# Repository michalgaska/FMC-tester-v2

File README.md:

# FMC-tester-v2

FMC tester v2 based on the original design done by Tomasz Wlostowski at CERN. The project was transferred to Kicad for Berkeley Lab.  
The following changes have been made:
- IO expanders were changed to MAX7312
- added resistors connecting _N and _P lines for each differential pair in the HPC signal group

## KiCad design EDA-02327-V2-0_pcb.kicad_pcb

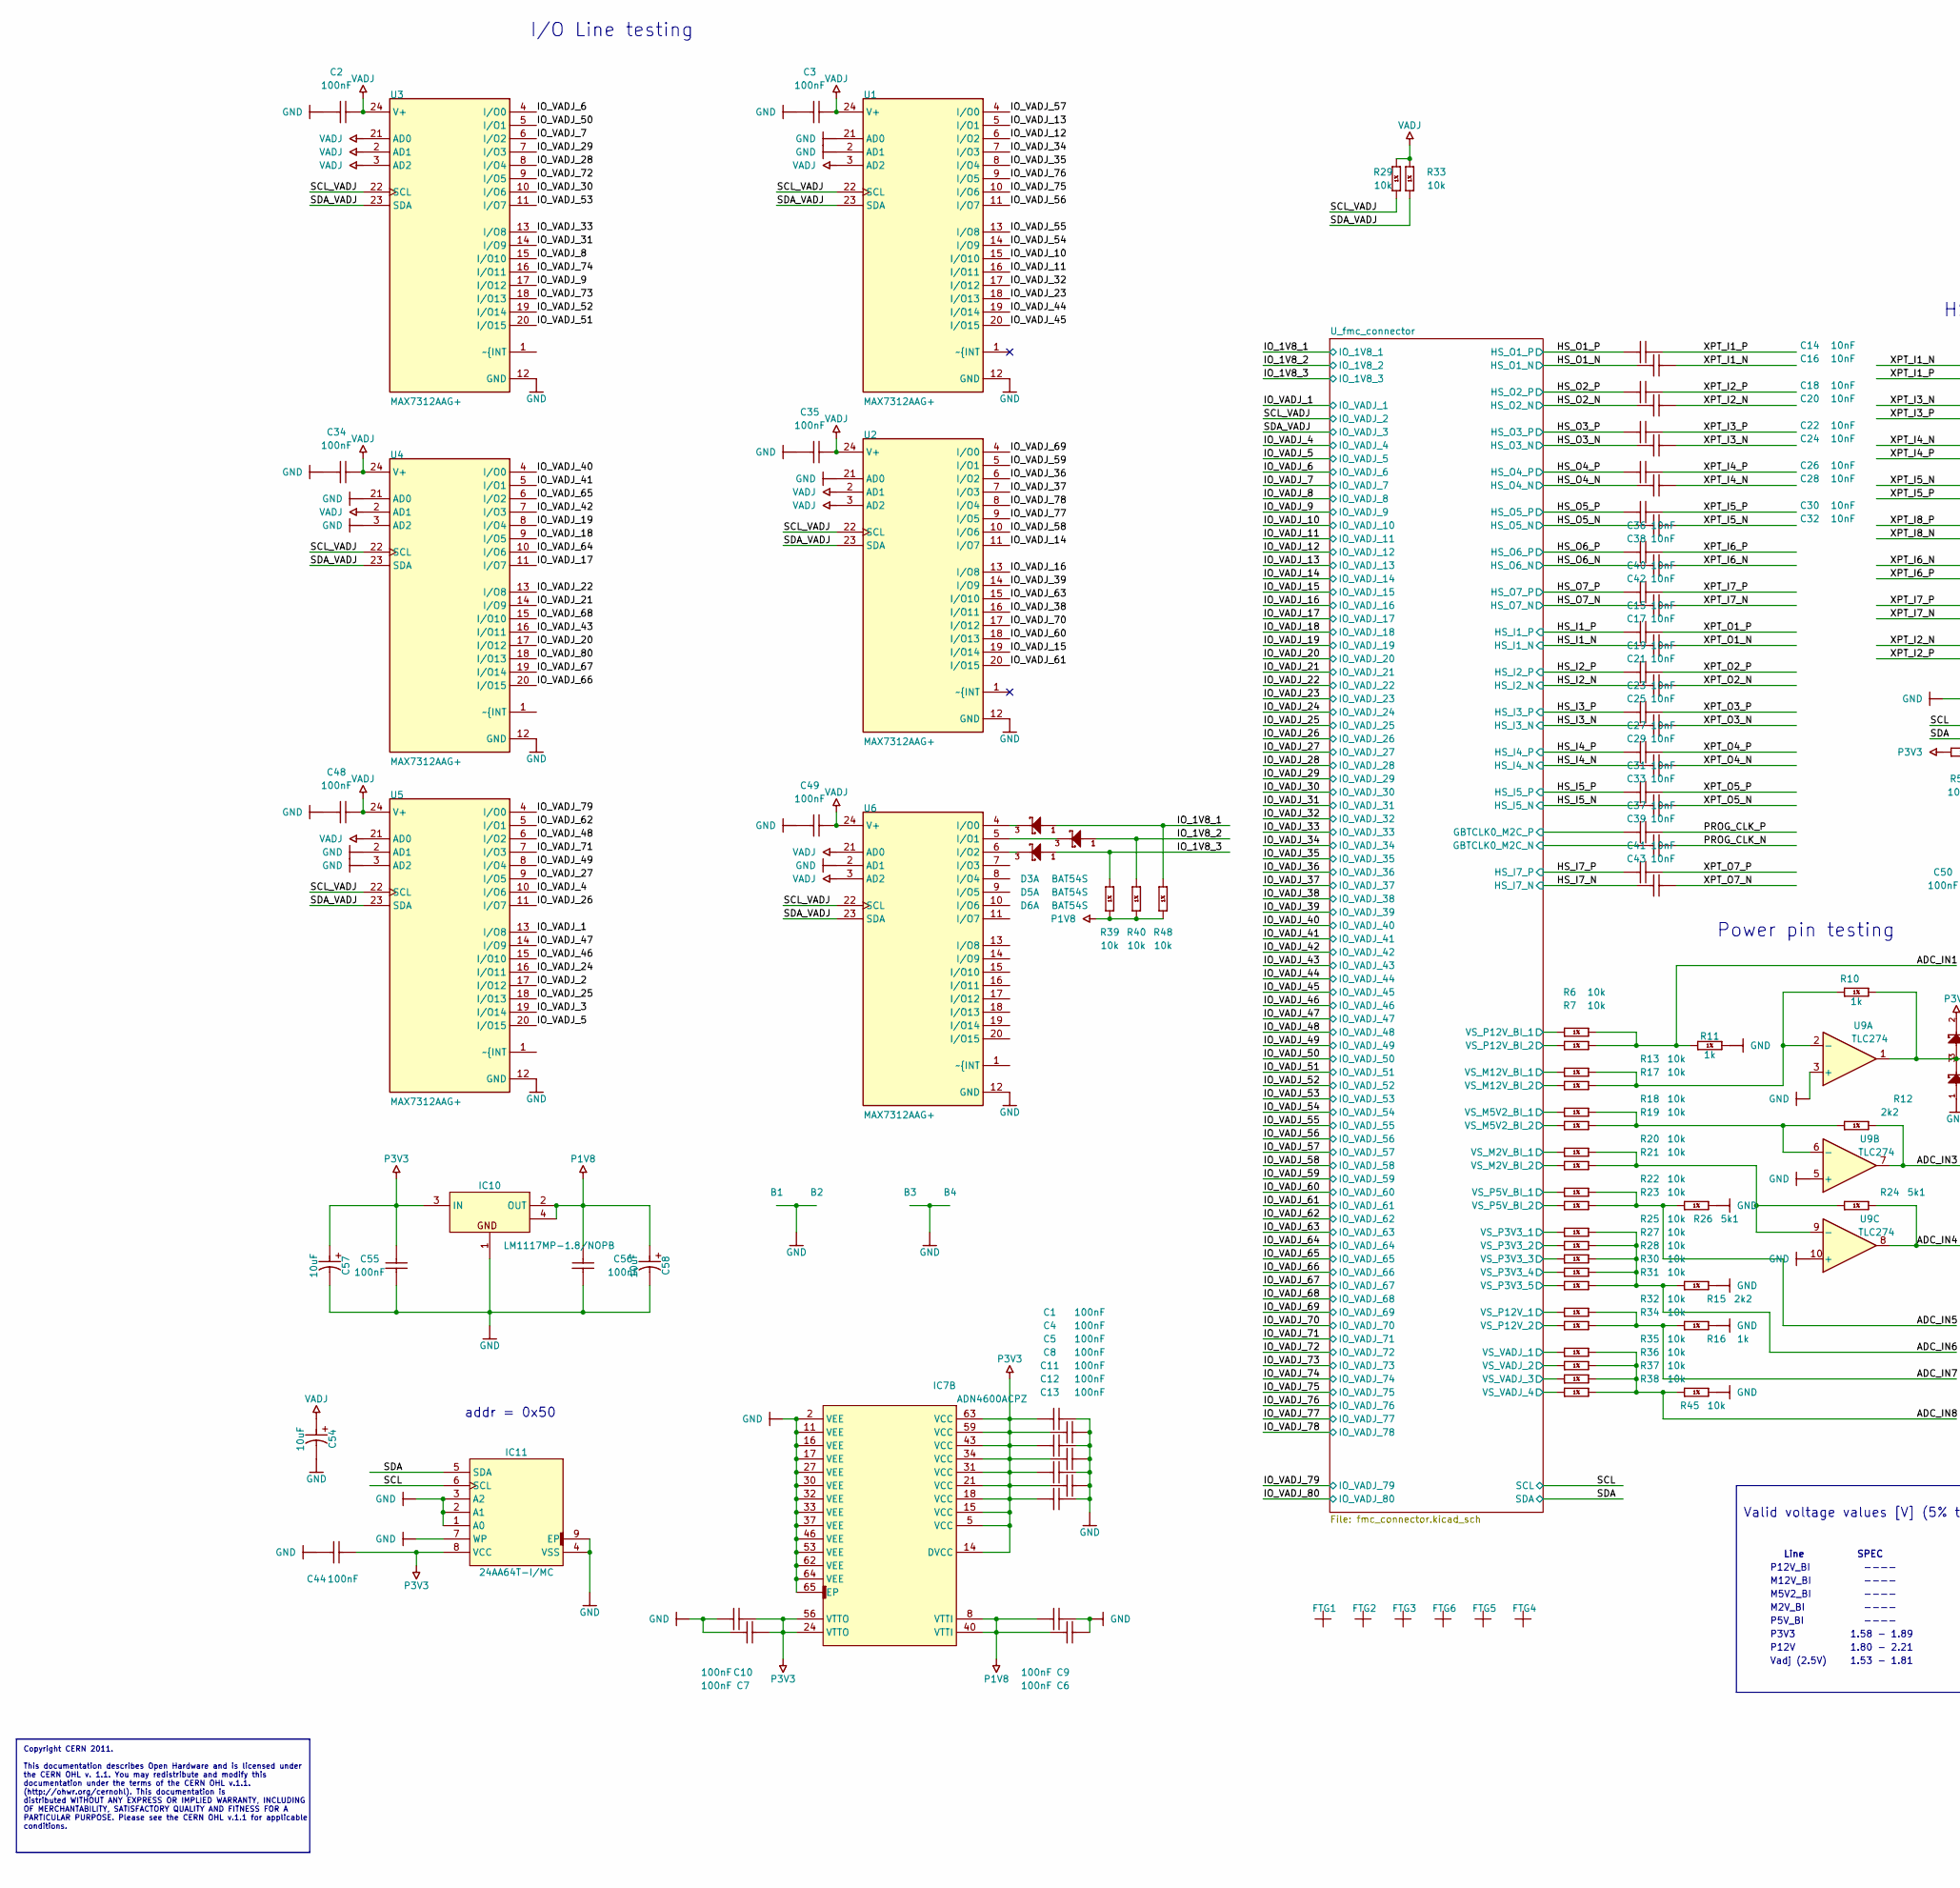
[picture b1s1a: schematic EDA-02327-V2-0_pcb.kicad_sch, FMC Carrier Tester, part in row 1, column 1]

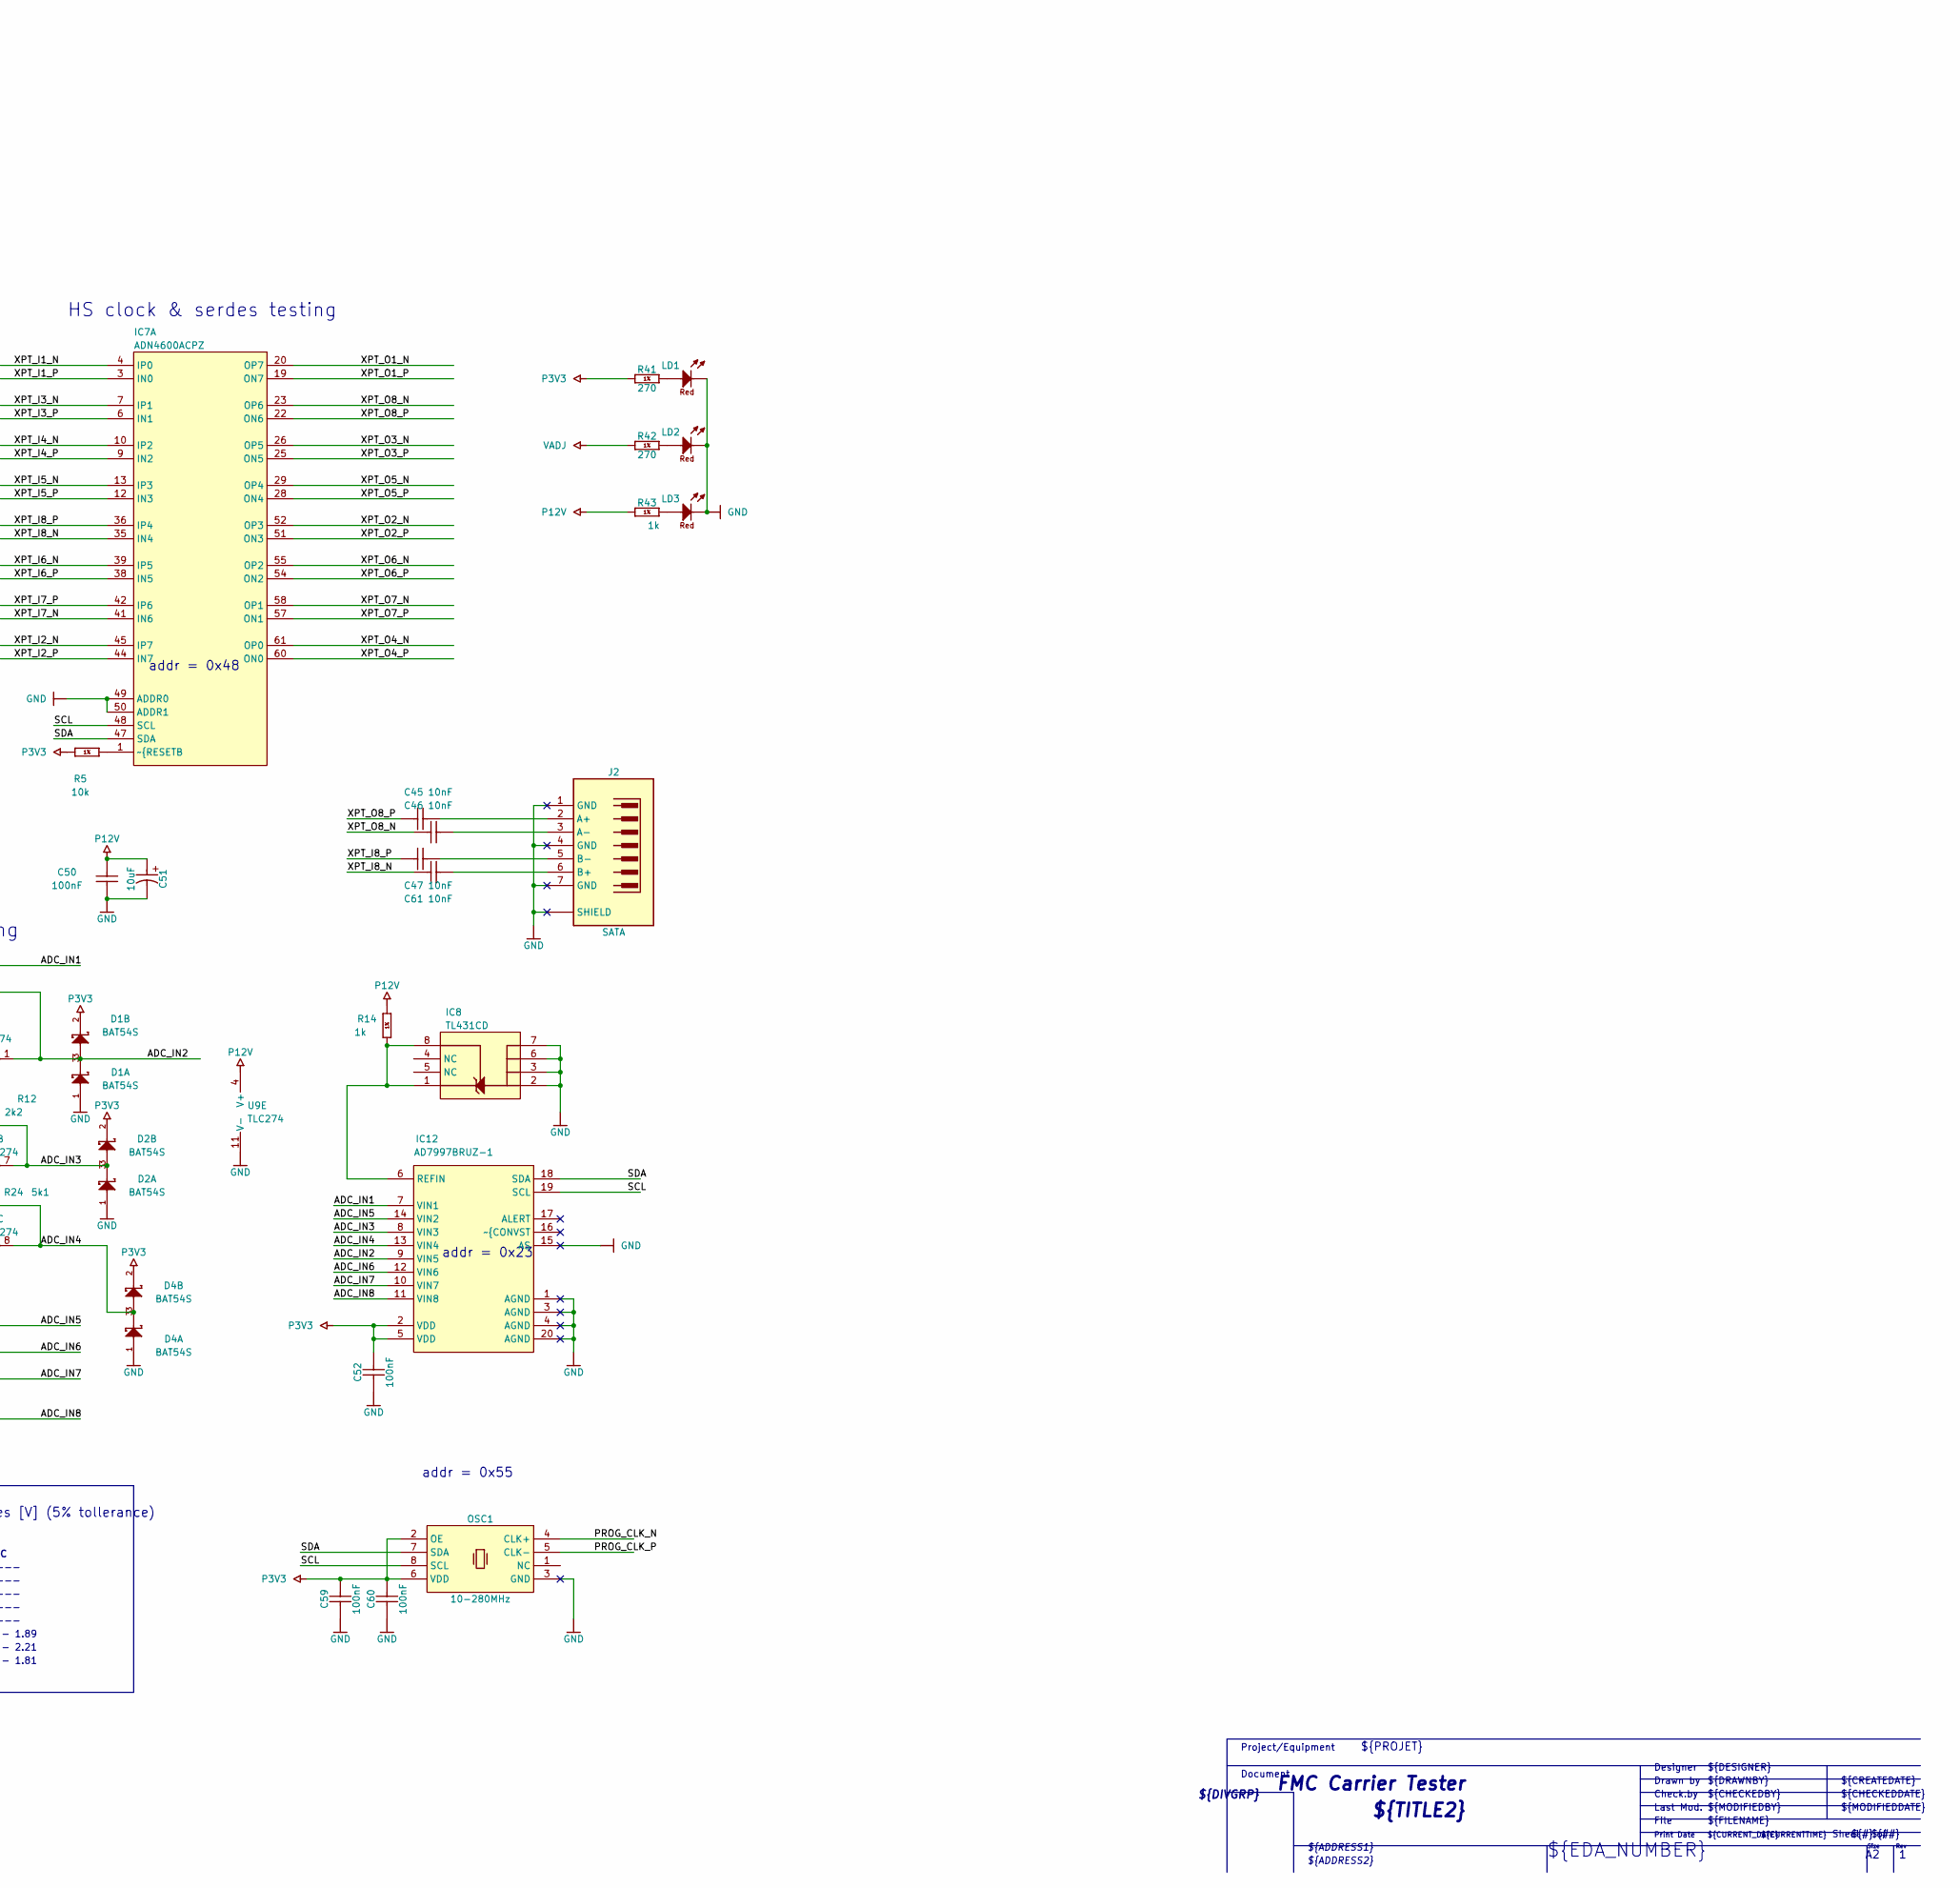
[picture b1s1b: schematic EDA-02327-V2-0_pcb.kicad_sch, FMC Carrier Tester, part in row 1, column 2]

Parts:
B1, B2, B3, B4: Plated Hole; MTG300_600; PART NUMBER PLATED_HOLE3.0_PAD6.0
C1, C2, C3, C4, C5, C6, C7, C8, C9, C10, C11, C12, C13, C34, C35, C44, C48, C49, C50, C52, C55, C56, C59, C60: 100nF; CAPC1608X87N; VOLTAGE 50V; TOLERANCE ±10%; PART NUMBER CC0603_100NF_50V_10%_X7R
C14, C15, C16, C17, C18, C19, C20, C21, C22, C23, C24, C25, C26, C27, C28, C29, C30, C31, C32, C33, C36, C37, C38, C39, C40, C41, C42, C43, C45, C46, C47, C61: 10nF; CAPC1005X55N; VOLTAGE 16V; TOLERANCE ±10%; PART NUMBER CC0402_10NF_16V_10%_X7R
C51, C54, C57, C58: 10uF; CAPMP3528X210N; VOLTAGE 16V; TOLERANCE ±10%; PART NUMBER CTE3528-21_10UF_16V_10%_LESR0800
D1, D2, D3, D4, D5, D6: BAT54S; SOT95P240X130-3N; VOLTAGE 30V; PART NUMBER BAT54S
FTG1, FTG2, FTG3, FTG4, FTG5, FTG6: Use only in PCB; FIDUCIAL_TOP_S100-200; PART NUMBER FIDUCIAL_TARGET_S100-200
IC7: ADN4600ACPZ; QFN50P900X900X100-65N-S615; PART NUMBER ADN4600ACPZ
IC8: TL431CD; SOIC127P600X175-8N; PART NUMBER TL431CD
IC10: LM1117MP-1.8/NOPB; SOT230P700X180-4N; PART NUMBER LM1117MP-1.8/NOPB
IC11: 24AA64T-I/MC; SON50P300X200X100-9N-S175X155; PART NUMBER 24AA64T-I/MC
IC12: AD7997BRUZ-1; SOP65P640X120-20N; PART NUMBER AD7997BRUZ-1
J2: SATA; 3M_5607-4200-SH; PART NUMBER 3M_5607-4200-SH
LD1, LD2, LD3: Red; LEDC1608X80N_RED; PART NUMBER LED_ROHM_SML-311UTT86K
OSC1: 10-280MHz; OSC_SILICON-LAB_SI570; PART NUMBER OSC_10-280MHZ_SILICON-LAB_Si570BBC00012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
R5, R6, R7, R13, R17, R18, R19, R20, R21, R22, R23, R25, R27, R28, R29, R30, R31, R32, R33, R34, R35, R36, R37, R38, R39, R40, R45, R48: 10k; RESC1608X55N; TOLERANCE ±1%; PART NUMBER R0603_10K_1%_0.1W_100PPM
R10, R11, R14, R16, R43: 1k; RESC1608X55N; TOLERANCE ±1%; PART NUMBER R0603_1K_1%_0.1W_100PPM
R12, R15: 2k2; RESC1608X55N; TOLERANCE ±1%; PART NUMBER R0603_2K2_1%_0.1W_100PPM
R24, R26: 5k1; RESC1608X55N; TOLERANCE ±1%; PART NUMBER R0603_5K1_1%_0.1W_100PPM
R41, R42: 270; RESC1608X55N; TOLERANCE ±1%; PART NUMBER R0603_270R_1%_0.1W_100PPM
U1, U2, U3, U4, U5, U6: MAX7312AAG+; FP-A24-2-MFG
U9: TLC274; SOIC-14_3.9x8.7mm_P1.27mm

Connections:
/ADC_IN1: IC12.7 (VIN1), R6.2, R7.2, R11.1
/ADC_IN2: D1.3 (COMAC), IC12.9 (VIN5), R10.2, U9.1
/ADC_IN3: D2.3 (COMAC), IC12.8 (VIN3), R12.2, U9.7
/ADC_IN4: D4.3 (COMAC), IC12.13 (VIN4), R24.2, U9.8
/ADC_IN5: IC12.14 (VIN2), R22.2, R23.2, R26.1
/ADC_IN6: IC12.12 (VIN6), R15.1, R25.2, R27.2, R28.2, R30.2, R31.2
/ADC_IN7: IC12.10 (VIN7), R16.1, R32.2, R34.2
/ADC_IN8: IC12.11 (VIN8), R35.2, R36.2, R37.2, R38.2, R45.1
/HS_I1_N: C17.1; also elsewhere on the board
/HS_I1_P: C15.1; also elsewhere on the board
/HS_I2_N: C21.1; also elsewhere on the board
/HS_I2_P: C19.1; also elsewhere on the board
/HS_I3_N: C25.1; also elsewhere on the board
/HS_I3_P: C23.1; also elsewhere on the board
/HS_I4_N: C29.1; also elsewhere on the board
/HS_I4_P: C27.1; also elsewhere on the board
/HS_I5_N: C33.1; also elsewhere on the board
/HS_I5_P: C31.1; also elsewhere on the board
/HS_I7_N: C43.1; also elsewhere on the board
/HS_I7_P: C41.1; also elsewhere on the board
/HS_O1_N: C16.1; also elsewhere on the board
/HS_O1_P: C14.1; also elsewhere on the board
/HS_O2_N: C20.1; also elsewhere on the board
/HS_O2_P: C18.1; also elsewhere on the board
/HS_O3_N: C24.1; also elsewhere on the board
/HS_O3_P: C22.1; also elsewhere on the board
/HS_O4_N: C28.1; also elsewhere on the board
/HS_O4_P: C26.1; also elsewhere on the board
/HS_O5_N: C32.1; also elsewhere on the board
/HS_O5_P: C30.1; also elsewhere on the board
/HS_O6_N: C38.1; also elsewhere on the board
/HS_O6_P: C36.1; also elsewhere on the board
/HS_O7_N: C42.1; also elsewhere on the board
/HS_O7_P: C40.1; also elsewhere on the board
/IO_1V8_1: D5.1 (A), R48.2; also elsewhere on the board
/IO_1V8_2: D6.1 (A), R40.2; also elsewhere on the board
/IO_1V8_3: D3.1 (A), R39.2; also elsewhere on the board
/IO_VADJ_1: U5.13 (I/O8); also elsewhere on the board
/IO_VADJ_2: U5.17 (I/O12)
/IO_VADJ_3: U5.19 (I/O14)
/IO_VADJ_4: U5.10 (I/O6); also elsewhere on the board
/IO_VADJ_5: U5.20 (I/O15); also elsewhere on the board
/IO_VADJ_6: U3.4 (I/O0); also elsewhere on the board
/IO_VADJ_7: U3.6 (I/O2); also elsewhere on the board
/IO_VADJ_8: U3.15 (I/O10); also elsewhere on the board
/IO_VADJ_9: U3.17 (I/O12); also elsewhere on the board
/IO_VADJ_10: U1.15 (I/O10); also elsewhere on the board
/IO_VADJ_11: U1.16 (I/O11); also elsewhere on the board
/IO_VADJ_12: U1.6 (I/O2); also elsewhere on the board
/IO_VADJ_13: U1.5 (I/O1); also elsewhere on the board
/IO_VADJ_14: U2.11 (I/O7); also elsewhere on the board
/IO_VADJ_15: U2.19 (I/O14); also elsewhere on the board
/IO_VADJ_16: U2.13 (I/O8); also elsewhere on the board
/IO_VADJ_17: U4.11 (I/O7); also elsewhere on the board
/IO_VADJ_18: U4.9 (I/O5); also elsewhere on the board
/IO_VADJ_19: U4.8 (I/O4); also elsewhere on the board
/IO_VADJ_20: U4.17 (I/O12); also elsewhere on the board
/IO_VADJ_21: U4.14 (I/O9); also elsewhere on the board
/IO_VADJ_22: U4.13 (I/O8); also elsewhere on the board
/IO_VADJ_23: U1.18 (I/O13); also elsewhere on the board
/IO_VADJ_24: U5.16 (I/O11); also elsewhere on the board
/IO_VADJ_25: U5.18 (I/O13); also elsewhere on the board
/IO_VADJ_26: U5.11 (I/O7); also elsewhere on the board
/IO_VADJ_27: U5.9 (I/O5); also elsewhere on the board
/IO_VADJ_28: U3.8 (I/O4); also elsewhere on the board
/IO_VADJ_29: U3.7 (I/O3); also elsewhere on the board
/IO_VADJ_30: U3.10 (I/O6); also elsewhere on the board
/IO_VADJ_31: U3.14 (I/O9); also elsewhere on the board
/IO_VADJ_32: U1.17 (I/O12); also elsewhere on the board
/IO_VADJ_33: U3.13 (I/O8); also elsewhere on the board
/IO_VADJ_34: U1.7 (I/O3); also elsewhere on the board
/IO_VADJ_35: U1.8 (I/O4); also elsewhere on the board
/IO_VADJ_36: U2.6 (I/O2); also elsewhere on the board
/IO_VADJ_37: U2.7 (I/O3); also elsewhere on the board
/IO_VADJ_38: U2.16 (I/O11); also elsewhere on the board
/IO_VADJ_39: U2.14 (I/O9); also elsewhere on the board
/IO_VADJ_40: U4.4 (I/O0); also elsewhere on the board
/IO_VADJ_41: U4.5 (I/O1); also elsewhere on the board
/IO_VADJ_42: U4.7 (I/O3); also elsewhere on the board
/IO_VADJ_43: U4.16 (I/O11); also elsewhere on the board
/IO_VADJ_44: U1.19 (I/O14); also elsewhere on the board
/IO_VADJ_45: U1.20 (I/O15); also elsewhere on the board
/IO_VADJ_46: U5.15 (I/O10); also elsewhere on the board
/IO_VADJ_47: U5.14 (I/O9); also elsewhere on the board
/IO_VADJ_48: U5.6 (I/O2); also elsewhere on the board
/IO_VADJ_49: U5.8 (I/O4); also elsewhere on the board
/IO_VADJ_50: U3.5 (I/O1); also elsewhere on the board
/IO_VADJ_51: U3.20 (I/O15); also elsewhere on the board
/IO_VADJ_52: U3.19 (I/O14); also elsewhere on the board
/IO_VADJ_53: U3.11 (I/O7); also elsewhere on the board
/IO_VADJ_54: U1.14 (I/O9); also elsewhere on the board
/IO_VADJ_55: U1.13 (I/O8); also elsewhere on the board
/IO_VADJ_56: U1.11 (I/O7); also elsewhere on the board
/IO_VADJ_57: U1.4 (I/O0); also elsewhere on the board
/IO_VADJ_58: U2.10 (I/O6); also elsewhere on the board
/IO_VADJ_59: U2.5 (I/O1); also elsewhere on the board
/IO_VADJ_60: U2.18 (I/O13); also elsewhere on the board
/IO_VADJ_61: U2.20 (I/O15); also elsewhere on the board
/IO_VADJ_62: U5.5 (I/O1); also elsewhere on the board
/IO_VADJ_63: U2.15 (I/O10); also elsewhere on the board
/IO_VADJ_64: U4.10 (I/O6); also elsewhere on the board
/IO_VADJ_65: U4.6 (I/O2); also elsewhere on the board
/IO_VADJ_66: U4.20 (I/O15); also elsewhere on the board
/IO_VADJ_67: U4.19 (I/O14); also elsewhere on the board
/IO_VADJ_68: U4.15 (I/O10); also elsewhere on the board
/IO_VADJ_69: U2.4 (I/O0); also elsewhere on the board
/IO_VADJ_70: U2.17 (I/O12); also elsewhere on the board
/IO_VADJ_71: U5.7 (I/O3); also elsewhere on the board
/IO_VADJ_72: U3.9 (I/O5); also elsewhere on the board
/IO_VADJ_73: U3.18 (I/O13); also elsewhere on the board
/IO_VADJ_74: U3.16 (I/O11); also elsewhere on the board
/IO_VADJ_75: U1.10 (I/O6); also elsewhere on the board
/IO_VADJ_76: U1.9 (I/O5); also elsewhere on the board
/IO_VADJ_77: U2.9 (I/O5); also elsewhere on the board
/IO_VADJ_78: U2.8 (I/O4); also elsewhere on the board
/IO_VADJ_79: U5.4 (I/O0); also elsewhere on the board
/IO_VADJ_80: U4.18 (I/O13); also elsewhere on the board
/PROG_CLK_N: C39.2, OSC1.4 (CLK+)
/PROG_CLK_P: C37.2, OSC1.5 (CLK-)
/SCL: IC7.48 (SCL), IC11.6 (SCL), IC12.19 (SCL), OSC1.8 (SCL); also elsewhere on the board
/SCL_VADJ: R29.1, U1.22 (SCL), U2.22 (SCL), U3.22 (SCL), U4.22 (SCL), U5.22 (SCL), U6.22 (SCL); also elsewhere on the board
/SDA: IC7.47 (SDA), IC11.5 (SDA), IC12.18 (SDA), OSC1.7 (SDA); also elsewhere on the board
/SDA_VADJ: R33.1, U1.23 (SDA), U2.23 (SDA), U3.23 (SDA), U4.23 (SDA), U5.23 (SDA), U6.23 (SDA); also elsewhere on the board
/U_fmc_connector/GBTCLK0_M2C_N: C39.1; also elsewhere on the board
/U_fmc_connector/GBTCLK0_M2C_P: C37.1; also elsewhere on the board
/U_fmc_connector/VS_M2V_BI_1: R20.1; also elsewhere on the board
/U_fmc_connector/VS_M2V_BI_2: R21.1; also elsewhere on the board
/U_fmc_connector/VS_M5V2_BI_1: R18.1; also elsewhere on the board
/U_fmc_connector/VS_M5V2_BI_2: R19.1; also elsewhere on the board
/U_fmc_connector/VS_M12V_BI_1: R13.1; also elsewhere on the board
/U_fmc_connector/VS_M12V_BI_2: R17.1; also elsewhere on the board
/U_fmc_connector/VS_P3V3_1: R25.1; also elsewhere on the board
/U_fmc_connector/VS_P3V3_2: R27.1; also elsewhere on the board
/U_fmc_connector/VS_P3V3_3: R28.1; also elsewhere on the board
/U_fmc_connector/VS_P3V3_4: R30.1; also elsewhere on the board
/U_fmc_connector/VS_P3V3_5: R31.1; also elsewhere on the board
/U_fmc_connector/VS_P5V_BI_1: R22.1; also elsewhere on the board
/U_fmc_connector/VS_P5V_BI_2: R23.1; also elsewhere on the board
/U_fmc_connector/VS_P12V_1: R32.1; also elsewhere on the board
/U_fmc_connector/VS_P12V_2: R34.1; also elsewhere on the board
/U_fmc_connector/VS_P12V_BI_1: R6.1; also elsewhere on the board
/U_fmc_connector/VS_P12V_BI_2: R7.1; also elsewhere on the board
/U_fmc_connector/VS_VADJ_1: R35.1; also elsewhere on the board
/U_fmc_connector/VS_VADJ_2: R36.1; also elsewhere on the board
/U_fmc_connector/VS_VADJ_3: R37.1; also elsewhere on the board
/U_fmc_connector/VS_VADJ_4: R38.1; also elsewhere on the board
/XPT_I1_N: C16.2, IC7.4 (IP0)
/XPT_I1_P: C14.2, IC7.3 (IN0)
/XPT_I2_N: C20.2, IC7.45 (IP7)
/XPT_I2_P: C18.2, IC7.44 (IN7)
/XPT_I3_N: C24.2, IC7.7 (IP1)
/XPT_I3_P: C22.2, IC7.6 (IN1)
/XPT_I4_N: C28.2, IC7.10 (IP2)
/XPT_I4_P: C26.2, IC7.9 (IN2)
/XPT_I5_N: C32.2, IC7.13 (IP3)
/XPT_I5_P: C30.2, IC7.12 (IN3)
/XPT_I6_N: C38.2, IC7.39 (IP5)
/XPT_I6_P: C36.2, IC7.38 (IN5)
/XPT_I7_N: C42.2, IC7.41 (IN6)
/XPT_I7_P: C40.2, IC7.42 (IP6)
/XPT_I8_N: C61.1, IC7.35 (IN4)
/XPT_I8_P: C47.1, IC7.36 (IP4)
/XPT_O1_N: C17.2, IC7.20 (OP7)
/XPT_O1_P: C15.2, IC7.19 (ON7)
/XPT_O2_N: C21.2, IC7.52 (OP3)
/XPT_O2_P: C19.2, IC7.51 (ON3)
/XPT_O3_N: C25.2, IC7.26 (OP5)
/XPT_O3_P: C23.2, IC7.25 (ON5)
/XPT_O4_N: C29.2, IC7.61 (OP0)
/XPT_O4_P: C27.2, IC7.60 (ON0)
/XPT_O5_N: C33.2, IC7.29 (OP4)
/XPT_O5_P: C31.2, IC7.28 (ON4)
/XPT_O6_N: IC7.55 (OP2)
/XPT_O6_P: IC7.54 (ON2)
/XPT_O7_N: C43.2, IC7.58 (OP1)
/XPT_O7_P: C41.2, IC7.57 (ON1)
/XPT_O8_N: C46.1, IC7.23 (OP6)
/XPT_O8_P: C45.1, IC7.22 (ON6)
GND: B1.1, B2.1, B3.1, B4.1, C1.2, C2.1, C3.1, C4.2, C5.2, C6.1, C7.2, C8.2, C9.1, C10.2, C11.2, C12.2, C13.2, C34.1, C35.1, C44.1, C48.1, C49.1, C50.1, C51.2, C52.1, C54.2, C55.1, C56.1, C57.2, C58.2, C59.1, C60.1, D1.1 (A), D2.1 (A), D4.1 (A), IC7.2 (VEE), IC7.11 (VEE), IC7.16 (VEE), IC7.17 (VEE), IC7.27 (VEE), IC7.30 (VEE), IC7.32 (VEE), IC7.33 (VEE), IC7.37 (VEE), IC7.46 (VEE), IC7.49 (ADDR0), IC7.50 (ADDR1), IC7.53 (VEE), IC7.62 (VEE), IC7.64 (VEE), IC7.65 (EP), IC8.2 (A), IC8.3 (A), IC8.6 (A), IC8.7 (A), IC10.1 (GND), IC11.1 (A0), IC11.2 (A1), IC11.3 (A2), IC11.4 (VSS), IC11.7 (WP), IC11.9 (EP), IC12.1 (AGND), IC12.3 (AGND), IC12.4 (AGND), IC12.15 (AS), IC12.20 (AGND), J2.1 (GND), J2.4 (GND), J2.7 (GND), J2.8 (SHIELD), LD1.1 (C), LD2.1 (C), LD3.1 (C), OSC1.3 (GND), R11.2, R15.2, R16.2, R26.2, R45.2, U1.2 (AD1), U1.12 (GND), U1.21 (AD0), U2.12 (GND), U2.21 (AD0), U3.12 (GND), U4.3 (AD2), U4.12 (GND), U4.21 (AD0), U5.2 (AD1), U5.3 (AD2), U5.12 (GND), U6.2 (AD1), U6.12 (GND), U9.3 (+), U9.5 (+), U9.10 (+), U9.11 (V-); also elsewhere on the board
unnamed: C45.2, J2.2 (A+)
unnamed: C46.2, J2.3 (A-)
unnamed: C47.2, J2.5 (B-)
unnamed: C61.2, J2.6 (B+)
unnamed: D3.3 (COMAC), U6.6 (I/O2)
unnamed: D5.3 (COMAC), U6.4 (I/O0)
unnamed: D6.3 (COMAC), U6.5 (I/O1)
unnamed: IC7.1 (~{RESETB), R5.2
unnamed: IC8.1 (C), IC8.8 (REF), IC12.6 (REFIN), R14.1
unnamed: LD1.2 (A), R41.2
unnamed: LD2.2 (A), R42.2
unnamed: LD3.2 (A), R43.2
unnamed: R10.1, R13.2, R17.2, U9.2 (-)
unnamed: R12.1, R18.2, R19.2, U9.6 (-)
unnamed: R20.2, R21.2, R24.1, U9.9 (-)
P1V8: C6.2, C9.2, C56.2, C58.1, IC7.8 (VTTI), IC7.40 (VTTI), IC10.2 (OUT), IC10.4 (OUT), R39.1, R40.1, R48.1
P3V3: C1.1, C4.1, C5.1, C7.1, C8.1, C10.1, C11.1, C12.1, C13.1, C44.2, C52.2, C55.2, C57.1, C59.2, C60.2, D1.2 (C), D2.2 (C), D4.2 (C), IC7.5 (VCC), IC7.14 (DVCC), IC7.15 (VCC), IC7.18 (VCC), IC7.21 (VCC), IC7.24 (VTTO), IC7.31 (VCC), IC7.34 (VCC), IC7.43 (VCC), IC7.56 (VTTO), IC7.59 (VCC), IC7.63 (VCC), IC10.3 (IN), IC11.8 (VCC), IC12.2 (VDD), IC12.5 (VDD), OSC1.2 (OE), OSC1.6 (VDD), R5.1, R41.1; also elsewhere on the board
P12V: C50.2, C51.1, R14.2, R43.1, U9.4 (V+); also elsewhere on the board
VADJ: C2.2, C3.2, C34.2, C35.2, C48.2, C49.2, C54.1, R29.2, R33.2, R42.1, U1.3 (AD2), U1.24 (V+), U2.2 (AD1), U2.3 (AD2), U2.24 (V+), U3.2 (AD1), U3.3 (AD2), U3.21 (AD0), U3.24 (V+), U4.2 (AD1), U4.24 (V+), U5.21 (AD0), U5.24 (V+), U6.3 (AD2), U6.21 (AD0), U6.24 (V+); also elsewhere on the board

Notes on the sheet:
${TITLE}
Size
${CHECKEDBY}
${DRAWNBY}
M5V2_BI
P5V_BI
P12V
SPEC
Copyright CERN 2011. This documentation describes Open Hardware and is licensed under the CERN OHL v. 1.1. You may redistribute and modify this documentation under the terms of the CERN OHL v.1.1. (http://ohwr.org/cernohl). This documentation is distributed WITHOUT ANY EXPRESS OR IMPLIED WARRANTY, 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
${PROJET}
${#}
Power pin testing
${DIVGRP}
${EDA_NUMBER}
${MODIFIEDDATE}
----
${CREATEDATE}
addr = 0x50
Valid voltage values [V] (5% tollerance)
Last Mod.
addr = 0x55
Rev
addr = 0x48
Designer
P12V_BI
I/O Line testing
Check.by
1.58 - 1.89
${ADDRESS2}
Vadj (2.5V)
${MODIFIEDBY}
1.53 - 1.81
Project/Equipment
addr = 0x23
${DESIGNER}
M12V_BI
${REVISION}
${CURRENT_DATE}
Drawn by
${CHECKEDDATE}

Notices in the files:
EDA-02327-V2-0_pcb.kicad_pcb:
Licensed under CERN OHL v 1.0
This documentation describes Open Hardware and is licensed under the CERN OHL v 1.0.
